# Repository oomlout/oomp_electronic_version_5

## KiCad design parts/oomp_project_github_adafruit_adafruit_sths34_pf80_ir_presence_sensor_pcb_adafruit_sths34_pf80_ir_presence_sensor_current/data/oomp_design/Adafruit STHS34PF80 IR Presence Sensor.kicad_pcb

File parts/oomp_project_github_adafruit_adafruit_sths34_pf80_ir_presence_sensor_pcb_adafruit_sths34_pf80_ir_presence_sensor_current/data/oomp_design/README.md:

# OOMP KiCad design copy

Open `Adafruit STHS34PF80 IR Presence Sensor.kicad_pro` (or the `.kicad_pcb` / `.kicad_sch`) in KiCad. Local OOMP libraries are under `libraries/`. Original inputs are preserved in [../original/](../original/).

Only verified unchanged installed KiCad defaults were renamed. Modified, custom, unmatched and unavailable items remain unchanged. Soldering variants are never swapped during conversion. Existing pad coordinates, nets and UUIDs are preserved.

See [conversion_report.yaml](conversion_report.yaml) for every conversion and skip. Copy this directory before editing; regeneration refuses to overwrite edited design files.

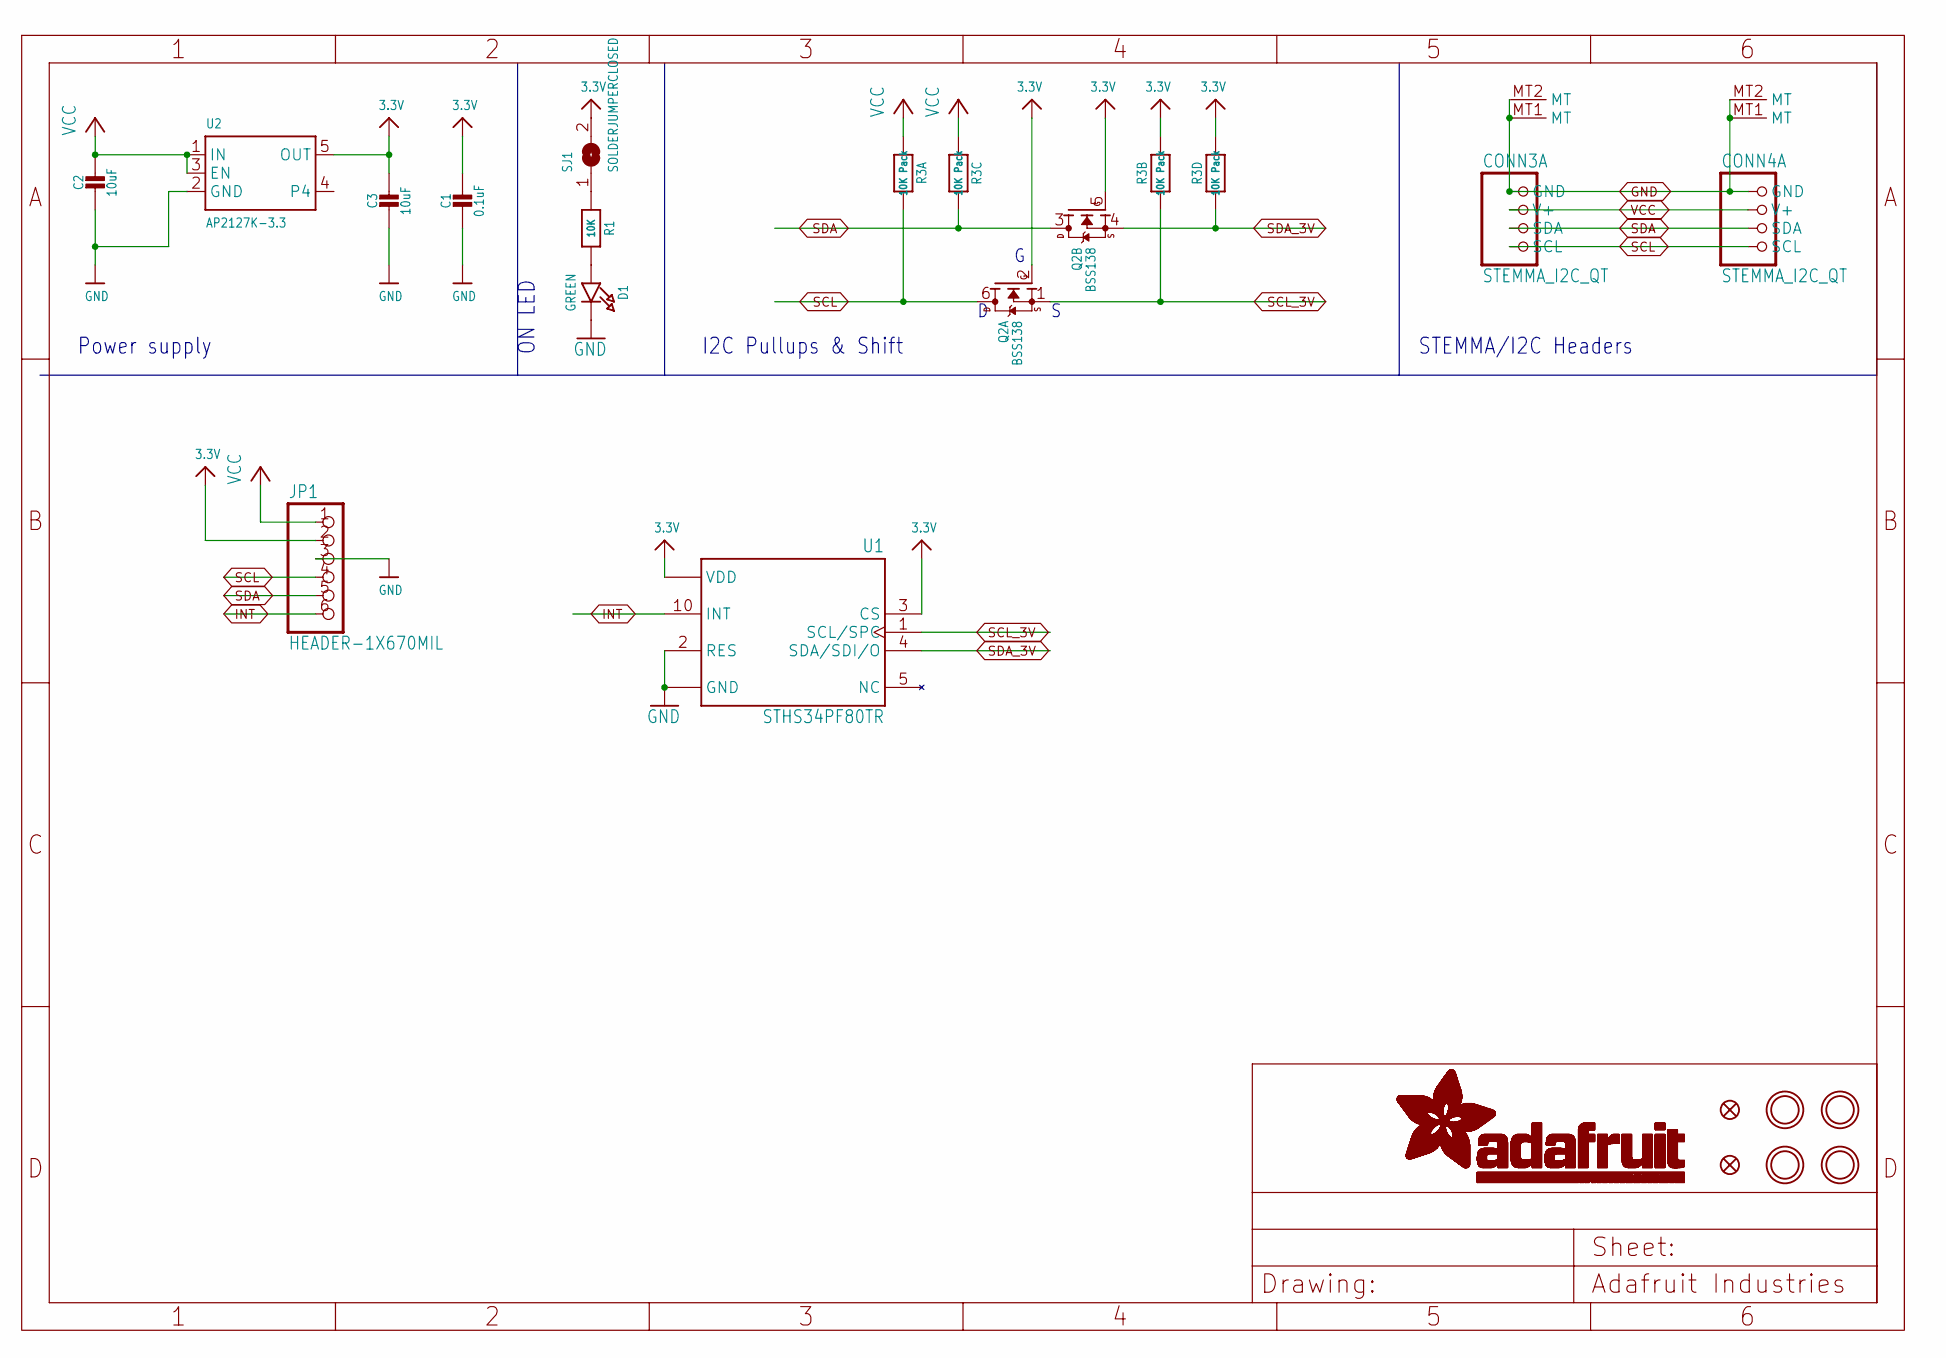
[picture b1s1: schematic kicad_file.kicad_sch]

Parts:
C1: 0.1uF; 0603-NO
C2, C3: 10uF; 0805-NO
CONN3, CONN4: STEMMA_I2C_QT; JST_SH4; LCSC C2845363
D1: GREEN; CHIPLED_0603_NOOUTLINE
FID3, FID4: FIDUCIAL_0.5MM
JP1: HEADER-1X670MIL; 1X06_ROUND_70
Q2: BSS138; SOT363; JLC_ROTATION 270
R1: 10K; 0603-NO
R3: 10K Pack; RESPACK_4X0603
SJ1: SOLDERJUMPERCLOSED; SOLDERJUMPER_CLOSEDWIRE
U1: STHS34PF80TR; XDCR_STHS34PF80TR; PARTREV 2
U2: AP2127K-3.3; SOT23-5; JLC_ROTATION 270
U$1, U$17, U$19, U$21: MOUNTINGHOLE2.5; MOUNTINGHOLE_2.5_PLATED

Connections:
3.3V: C1.1, C3.1, JP1.2, Q2.2 (G), Q2.5 (G), R3.2 (1), R3.4 (1), SJ1.2, U1.3 (CS), U1.6 (VDD), U1.9 (VDD), U2.5 (OUT)
GND: C1.2, C2.2, C3.2, CONN3.1 (GND), CONN3.MT1 (MT), CONN3.MT2 (MT), CONN4.1 (GND), CONN4.MT1 (MT), CONN4.MT2 (MT), D1.C, JP1.3, U1.2 (RES), U1.7 (GND), U1.8 (GND), U2.2 (GND)
INT: JP1.6, U1.10 (INT)
unnamed: D1.A, R1.2
unnamed: R1.1, SJ1.1
SCL: CONN3.4 (SCL), CONN4.4 (SCL), JP1.4, Q2.6 (D), R3.8 (2)
SCL_3V: Q2.1 (S), R3.7 (2), U1.1 (SCL/SPC)
SDA: CONN3.3 (SDA), CONN4.3 (SDA), JP1.5, Q2.3 (D), R3.6 (2)
SDA_3V: Q2.4 (S), R3.5 (2), U1.4 (SDA/SDI/O)
VCC: C2.1, CONN3.2 (V+), CONN4.2 (V+), JP1.1, R3.1, R3.3 (1), U2.1 (IN), U2.3 (EN)

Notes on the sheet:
Power supply
ON LED
STEMMA/I2C Headers
I2C Pullups & Shift

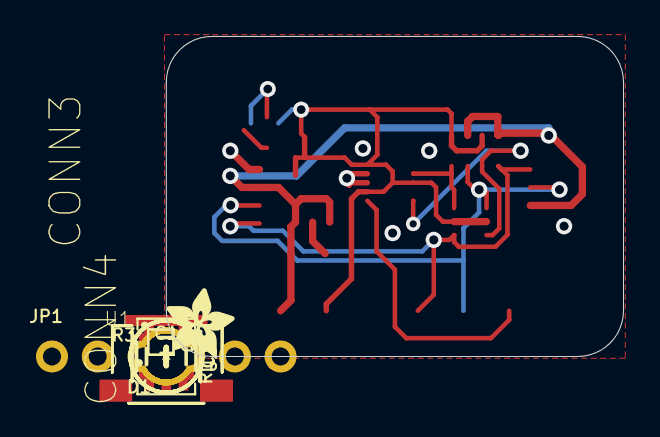
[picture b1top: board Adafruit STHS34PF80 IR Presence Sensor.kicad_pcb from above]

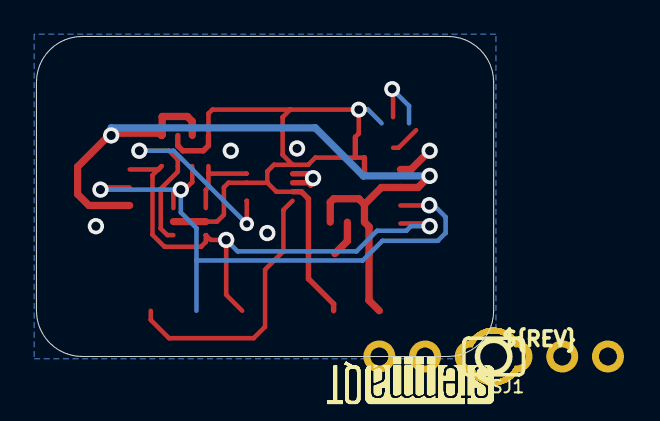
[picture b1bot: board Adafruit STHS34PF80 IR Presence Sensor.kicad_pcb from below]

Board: 2 copper layers, 25.4 x 17.8 mm, 36 parts (8 on the bottom side), 10 nets.

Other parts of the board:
PLABEL0: PLABEL0
PLABEL1: PLABEL1
PLABEL2: PLABEL2
PLABEL3: PLABEL3
PLABEL4: PLABEL4
PLABEL5: PLABEL5
PLABEL6: PLABEL6
PLABEL7: PLABEL7
PLABEL8: PLABEL8
PLABEL9: PLABEL9
PLABEL10: PLABEL10
PLABEL11: PLABEL11
PLABEL12: PLABEL12
U$22: ADAFRUIT_3.5MM
U$25: PCBFEAT-REV-040
U$30, U$31: STEMMAQT

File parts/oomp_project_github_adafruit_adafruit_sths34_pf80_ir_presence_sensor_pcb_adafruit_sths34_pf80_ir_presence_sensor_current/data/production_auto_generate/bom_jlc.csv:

Comment,Designator,Footprint,LCSC Part #
,JP1,Adafruit STHS34PF80 IR Presence Sensor-import-fps:1X06_ROUND_70,C37208
,U$22,Adafruit STHS34PF80 IR Presence Sensor-import-fps:ADAFRUIT_3.5MM,
,U$25,Adafruit STHS34PF80 IR Presence Sensor-import-fps:PCBFEAT-REV-040,
,PLABEL0,Adafruit STHS34PF80 IR Presence Sensor-import-fps:PLABEL0,
,PLABEL1,Adafruit STHS34PF80 IR Presence Sensor-import-fps:PLABEL1,
,PLABEL10,Adafruit STHS34PF80 IR Presence Sensor-import-fps:PLABEL10,
,PLABEL11,Adafruit STHS34PF80 IR Presence Sensor-import-fps:PLABEL11,
,PLABEL12,Adafruit STHS34PF80 IR Presence Sensor-import-fps:PLABEL12,
,PLABEL2,Adafruit STHS34PF80 IR Presence Sensor-import-fps:PLABEL2,
,PLABEL3,Adafruit STHS34PF80 IR Presence Sensor-import-fps:PLABEL3,
,PLABEL4,Adafruit STHS34PF80 IR Presence Sensor-import-fps:PLABEL4,
,PLABEL5,Adafruit STHS34PF80 IR Presence Sensor-import-fps:PLABEL5,
,PLABEL6,Adafruit STHS34PF80 IR Presence Sensor-import-fps:PLABEL6,
,PLABEL7,Adafruit STHS34PF80 IR Presence Sensor-import-fps:PLABEL7,
,PLABEL8,Adafruit STHS34PF80 IR Presence Sensor-import-fps:PLABEL8,
,PLABEL9,Adafruit STHS34PF80 IR Presence Sensor-import-fps:PLABEL9,
,"U$30,U$31",Adafruit STHS34PF80 IR Presence Sensor-import-fps:STEMMAQT,
0.1uF,C1,Adafruit STHS34PF80 IR Presence Sensor-import-fps:0603-NO,C14663
10K,R1,Adafruit STHS34PF80 IR Presence Sensor-import-fps:0603-NO,C98220
10K Pack,R3,Adafruit STHS34PF80 IR Presence Sensor-import-fps:RESPACK_4X0603,C98220
10uF,"C2,C3",Adafruit STHS34PF80 IR Presence Sensor-import-fps:0805-NO,
AP2127K-3.3,U2,Adafruit STHS34PF80 IR Presence Sensor-import-fps:SOT23-5,
BSS138,Q2,Adafruit STHS34PF80 IR Presence Sensor-import-fps:SOT363,
GREEN,D1,Adafruit STHS34PF80 IR Presence Sensor-import-fps:CHIPLED_0603_NOOUTLINE,
STEMMA_I2C_QT,"CONN3,CONN4",Adafruit STHS34PF80 IR Presence Sensor-import-fps:JST_SH4,C160404
STHS34PF80TR,U1,Adafruit STHS34PF80 IR Presence Sensor-import-fps:XDCR_STHS34PF80TR,

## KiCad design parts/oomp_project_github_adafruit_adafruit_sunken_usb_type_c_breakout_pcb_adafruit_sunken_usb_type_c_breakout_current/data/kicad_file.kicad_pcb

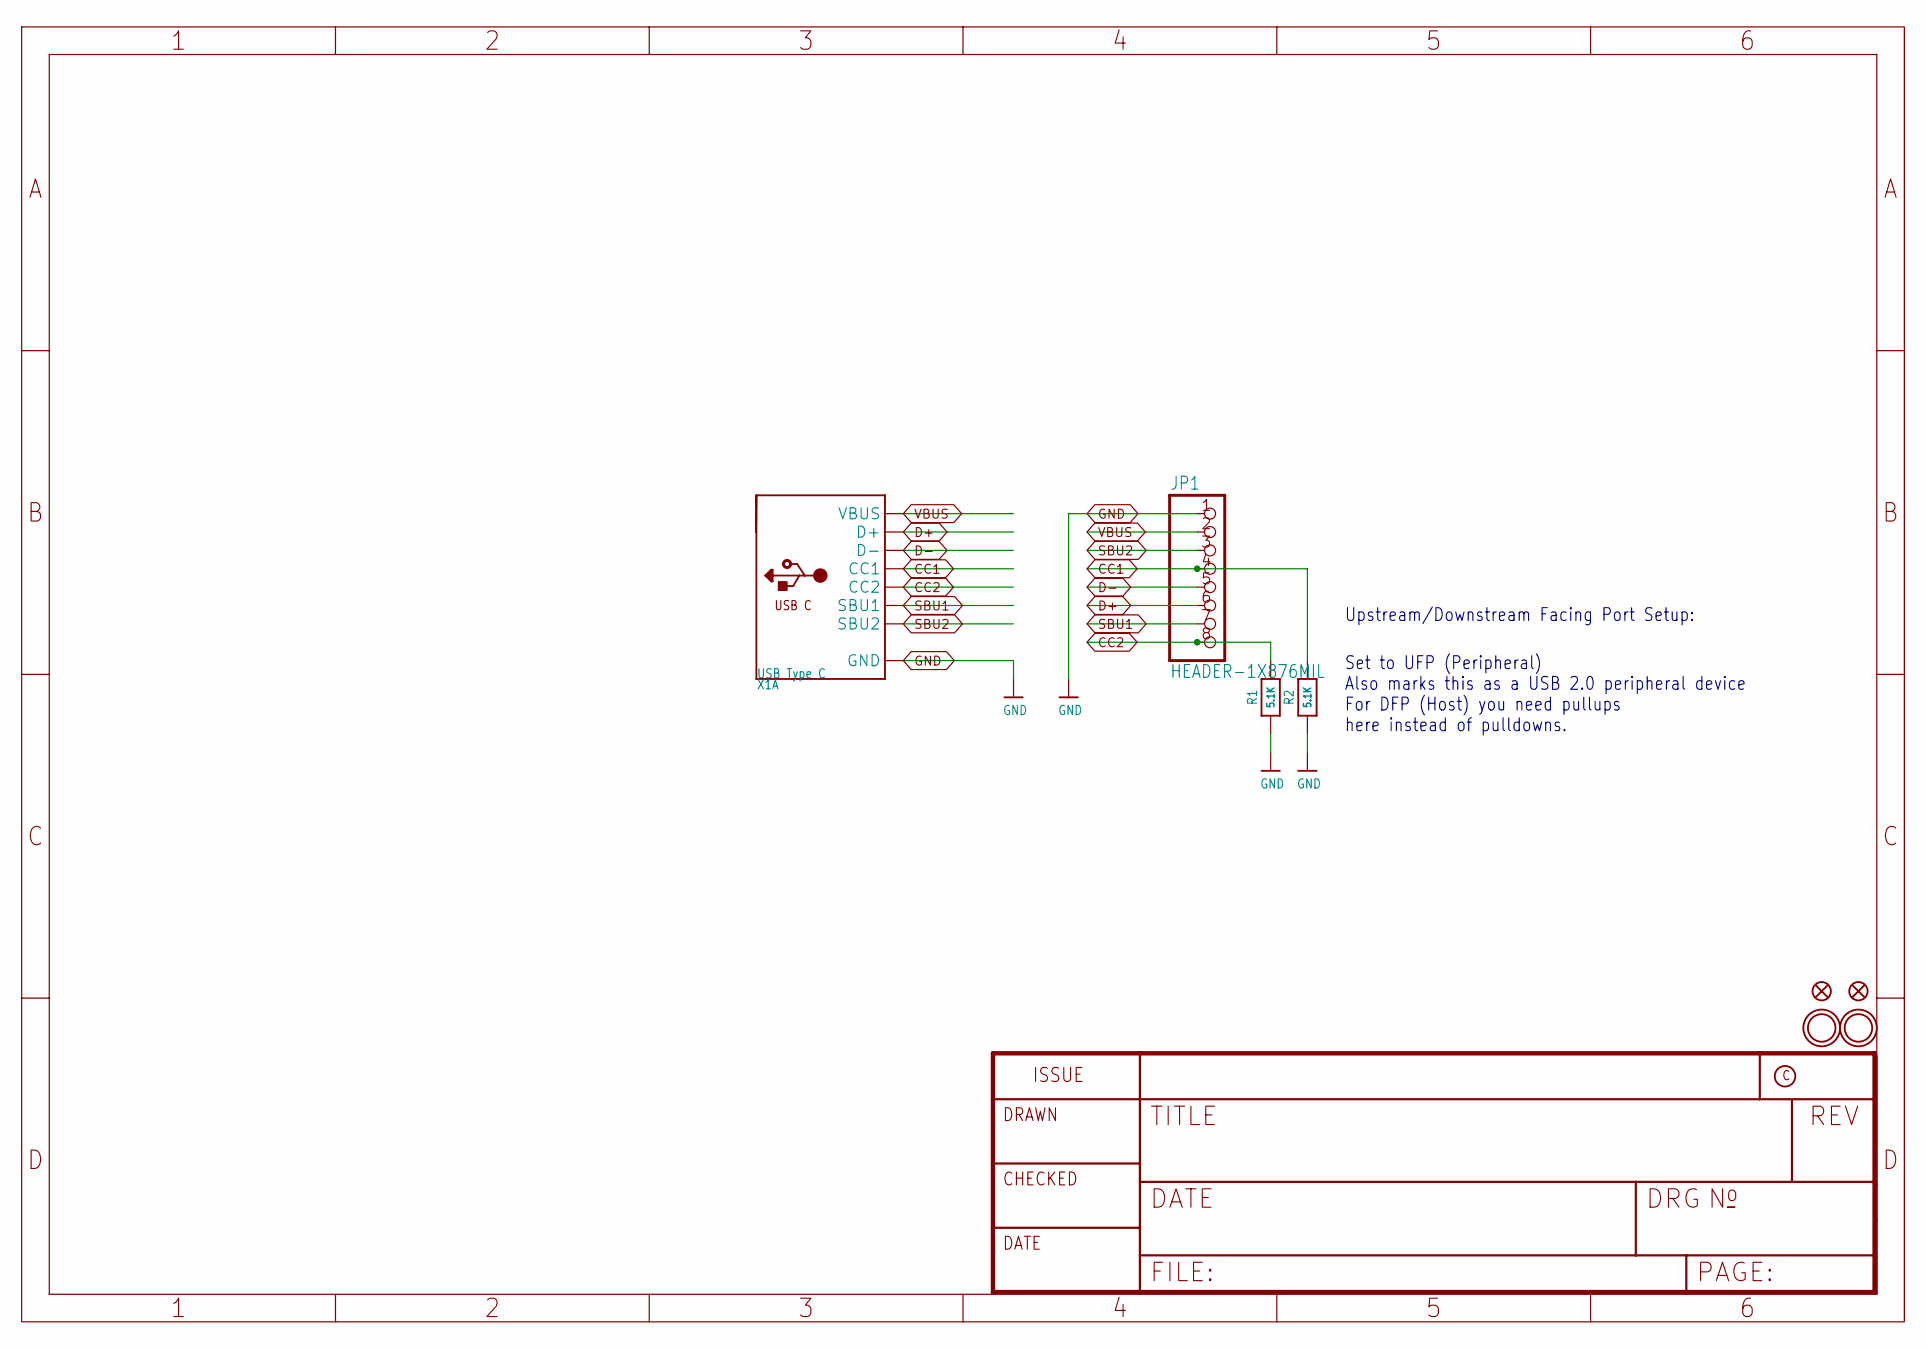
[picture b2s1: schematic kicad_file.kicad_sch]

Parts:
FID1, FID2: FIDUCIAL_0.5MM
JP1: HEADER-1X876MIL; 1X08_ROUND_76
R1, R2: 5.1K; 0603-NO
U$1, U$2: MOUNTINGHOLE2.5; MOUNTINGHOLE_2.5_PLATED
X1: USB Type C; USB_C_SINK

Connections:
CC1: JP1.4, R2.2, X1.A5 (CC1)
CC2: JP1.8, R1.2, X1.B5 (CC2)
D+: JP1.6, X1.A6 (D+), X1.B6 (D+)
D-: JP1.5, X1.A7 (D-), X1.B7 (D-)
GND: JP1.1, R1.1, R2.1, X1.A1B12 (GND), X1.B1A12 (GND)
SBU1: JP1.7, X1.A8 (SBU1)
SBU2: JP1.3, X1.B8 (SBU2)
VBUS: JP1.2, X1.A4B9 (VBUS), X1.B4A9 (VBUS)

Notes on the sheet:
Set to UFP (Peripheral) Also marks this as a USB 2.0 peripheral device For DFP (Host) you need pullups here instead of pulldowns.
Upstream/Downstream Facing Port Setup:

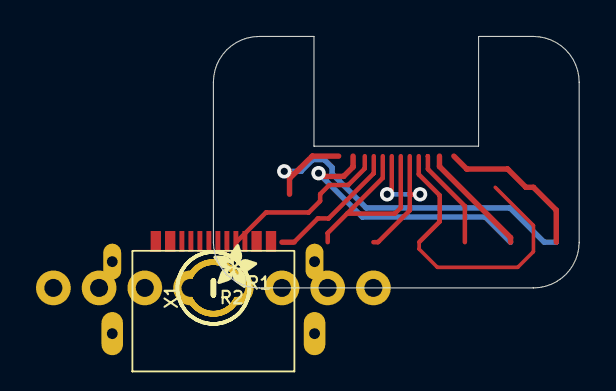
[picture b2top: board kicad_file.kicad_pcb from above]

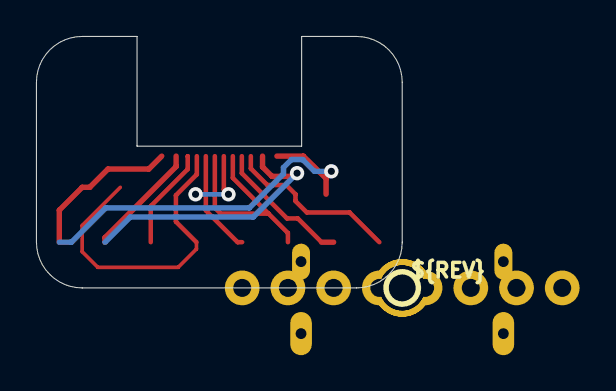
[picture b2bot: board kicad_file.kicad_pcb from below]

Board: 2 copper layers, 20.3 x 14.0 mm, 21 parts (3 on the bottom side), 8 nets.

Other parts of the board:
PLABEL0: PLABEL0
PLABEL1: PLABEL1
PLABEL2: PLABEL2
PLABEL3: PLABEL3
PLABEL4: PLABEL4
PLABEL5: PLABEL5
PLABEL6: PLABEL6
PLABEL7: PLABEL7
PLABEL8: PLABEL8
PLABEL9: PLABEL9
PLABEL10: PLABEL10
U$3: ADAFRUIT_2.5MM
U$8: PCBFEAT-REV-040
